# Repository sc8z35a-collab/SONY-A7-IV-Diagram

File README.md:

# @FLOW_BOOK 2: DOMAIN_SPEC (SONY-A7-IV-Diagram | FLOW-SPEC/v1.1)
> AUDIENCE=AI_AGENTS_ONLY | COMPANION=AGENTS.md (Book 1: ENV_OS) | QUERY: `npm run flow -- doc section 2 <@TAG>`

## @PROJECT_MAP
- App: Sony A7 IV Full-Frame Mirrorless Camera + Special Showcases (`welcome` WLK-435 CNC optical signboard, `original` Exhibit #01 RIIMOS E1 9,700 JPY quadruped, `mirai_2028` 2028 Frontier concepts, `sensor_fab` 6-vol semiconductor fab) 3D CAD WebGL2 Technical Anatomy + Play Ground 1.1 Studio (`PLYA V2.1`).
<!-- @FLOW_AUTO:PROJECT_METRICS -->
- Stack: TypeScript 5.8.2 + Three.js 0.174.0 + Vite 6.2.0 (`dist/` -> `docs/`) + Capacitor 7.6.10 (`android/`).
- Scale: 23 modes (21 individual + 2 composite), 2,937 unique individual parts (3,473 total entries incl. composites), PLYA V2.1 (24 browser solvers / 256 assertions).
<!-- /@FLOW_AUTO:PROJECT_METRICS -->
- Schematics & Rigs: 720x470 HD SVG schematics (`src/ui/schematicsRegistry.ts`), 60fps physics rigs.
- Protected Content Assets (NOT operational manuals): `reports/fh_mirai_2028/*.md` (compiled by `scripts/build_mirai_content.mjs`) and `blueprints/riimos_e1/` (RIIMOS E1 MJCF/Colab/blueprint assets).

## @RENDER_V2_V3_AND_PLYA_V21
- Universal V2 (`src/core/v2_unit_compiler.ts`): All units except bespoke `src/units/mi_shoe.ts` compile via `CompiledV2Unit` -> `ResourceCache` 38 PBR buckets (`src/core/resource_cache.ts`, 0 raw materials), `InstancedMesh`/`BatchedMesh`, flat TypedArray AABB-BVH (`bvhNodes`, stride 8) O(log N) 0-GC raycast, GPU shader explode, `disposeObject3D` VRAM leak=0, plus live cryptographic **`V1.1証明`** verifier (`src/core/v11_seal_verifier.ts`, `src/units/v1_1_certificates.gen.ts`) & clickable HUD warranty modal (`src/ui/ZeroTextControls.ts`).
- 4 Quality Tiers: `standard_lite` (Dual-Atlas Single-Bucket Fusion, ~2-8 draw calls, 16-bit Uint16 IBOs <=65k verts, Fresnel rim, spatial-hash weld); `standard`/`high`/`ultra` (progressive radial segments, 9k/18k/32k batched CAD edges, PMREM IBL, ULTRA zero-jaggy AA).
- Play Ground 1.1 + **`PLYA V2.1 (THE LAST EXAM V1.1 Inherited)`**: `src/playground/CadPlaygroundStudio.ts`, `PlyaVerificationPipeline.ts`, `exam_core/BrowserPhysicsSolvers.ts`, `exam_core/V11BrowserSolversExt.ts`. **12 Pillars / 24 Browser Solvers / 256 Atomic Assertions (`PG-T001..PG-T256`)**, Real-World Boot Readiness % & Six-Sigma Manufacturing Yield % meters, `.tlx11.json` export (`TLX11-PLAYGROUND-BLUEPRINT-V1.1`, bit-exact 0.0001mm canonical 3D SHA-256 parity with `ir_compiler.mjs`), `.v1_1.cert.json` import + **instant automatic V1.1証明 revocation on ANY 3D edit**.
- V3 10 Pillars: Play Ground 1.1 Hyper-Engine (40.05x avg speedup, 0.0 idle draws/s); STD LITE v2 (14.45x arith / 3.23x geo, 0.00% black-crush); ULTRA zero-jaggy AA; Adaptive `FAST<->LITE<->ULTRA` & `PG_FAST<->PG_LITE<->PG_SHARP`; `KINE` 3-layer 0-GC occlusion culling; 16x macro zoom; Load-guarded F1.2 bokeh (`auto`); Vivid electric-blue selection (`CAD_SELECT_SENTINEL`); Mobile 390x844@2 landscape UI & 90-deg lightbox; Locked camera angle in detail view.

## @UNIT_REGISTRY (23 MODES: mode | kind | parts | slug | codes | exam | entry | data)
- `welcome` | indiv | 435 | `welcome-` | W01..W435 | YES | `src/units/welcome.ts` | `src/data/welcome.json`
- `original` | indiv | 128 | `orig-` | OR01..OR128 | YES | `src/units/original.ts` | `src/data/original.json`
- `mishoe` | indiv | 99 | `mi-` | MI01..MI99 | YES | `src/units/mi_shoe.ts`* | `src/data/mi_shoe.json`
- `battery` | indiv | 130 | `bat-` | P01..P130 | YES | `src/units/battery.ts` | `src/data/battery.json`
- `cfexpress` | indiv | 170 | `cfe-` | C01..C170 | YES | `src/units/cfexpress.ts` | `src/data/cfexpress.json`
- `mic` | indiv | 150 | `mc-` | MC01..MC150 | YES | `src/units/mic.ts` | `src/data/mic.json`
- `drybox` | indiv | 186 | `db-` | DB01..DB186 | YES | `src/units/drybox.ts` | `src/data/drybox.json`
- `mount` | indiv | 100 | `mount-` | M22..M100 | YES | `src/units/mount.ts` | `src/data/mount.json`
- `shutter` | indiv | 180 | `shutter-` | SH34..SH180 | YES | `src/units/shutter.ts` | `src/data/shutter.json`
- `body` | indiv | 116 | `body-` | B01..B116 | YES | `src/units/body.ts` | `src/data/body.json`
- `evf` | indiv | 105 | `evf-` | E26..E105 | YES | `src/units/evf.ts` | `src/data/evf.json`
- `lcd` | indiv | 150 | `lcd-` | D01..D150 | YES | `src/units/lcd.ts` | `src/data/lcd.json`
- `lens` | indiv | 128 | `lens-` | L01..L128 | YES | `src/units/lens.ts` | `src/data/lens.json`
- `mainboard` | indiv | 60 | `mb-` | M17..M60 | YES | `src/units/mainboard.ts` | `src/data/mainboard.json`
- `bionz` | indiv | 70 | `xr-` | XR01..XR70 | YES | `src/units/bionz.ts` | `src/data/bionz.json`
- `bionz_v2` | indiv | 105 | `xv2-` | X2-01..X2-105 | YES | `src/units/bionz_v2.ts` | `src/data/bionz_v2.json`
- `sensor` | indiv | 120 | `sensor-` | S35..S120 | YES | `src/units/sensor.ts` | `src/data/sensor.json`
- `micro` | indiv | 75 | `micro-` | M12..M75 | YES | `src/units/micro.ts` | `src/data/micro.json`
- `micro_v2` | indiv | 55 | `pv2-` | P2-01..P2-55 | YES | `src/units/micro_v2.ts` | `src/data/micro_v2.json`
- `sensor_fab` | indiv | 235 | `fab5-` | F0-01..F5-38 | EXCL | `src/units/sensor_fab.ts` | `src/data/sensor_fab.json`
- `mirai_2028` | indiv | 140 | `mirai-` | FH01-01..FH48-18 | EXCL | `src/units/mirai_2028.ts` | `src/data/mirai_2028.json`
- `integrated` | comp | 305 | - | - | YES | `src/units/integrated.ts` | `src/data/integrated.json`
- `camera_body` | comp | 231 | - | - | YES | `src/units/camera_body.ts` | `src/data/camera_body.json`
- Note `*`: `mi_shoe.ts` implements `OptimizedUnit` directly, calls `applyUnitPoseTable()`, and attaches `v11Certification` for 23/23 parity.
- Sub-views: `lensSection=1..3`, `fabVolume=0..5`, `miraiSubView=1..5` (`beginner|expert`), `original` RIIMOS E1 (128p, 9,700 JPY BOM, 0.135J 8-barrel quadruped, L4 MJCF).

## @UNIT_DEPENDENCY_DAG (21 EXAM TARGETS + 2 EXCLUDED)
- **Stage 1 — 19 Independent EXAM Units (parallel-safe)**: `welcome, original, mishoe, battery, cfexpress, mic, drybox, mount, shutter, body, evf, lcd, lens, mainboard, bionz, bionz_v2, sensor, micro, micro_v2`.
- **Stage 2 — 2 Composite EXAM Units (MUST run AFTER Stage 1)**: `camera_body` (231p, depends on 7 Stage-1 builders: `mount, body, evf, shutter, sensor[macroParts], mainboard, lcd`) and `integrated` (305p, depends on all 8 Stage-1 builders: `lens, mount, body, evf, shutter, sensor[macroParts], mainboard, lcd`) via shared `src/units/camera_macro_shared.ts`.
- **EXAM Excluded (`EXCLUDED_EXAM_UNITS`)**: `mirai_2028` (140p), `sensor_fab` (235p).
<!-- @FLOW_AUTO:UNIT_HEALTH_SUMMARY -->
- Live Health Baseline (SSOT `catalog/UNIT_HEALTH.tsv` + `verification/certificates/` + `src/units/*.pose.tsv`): **Certified=`0/21`** | **Full-Clean (0 clash & 0 EX02 >0.08mm gap)=`0/21`** (`none`) | **0-Clash/Explode=`2/21`** (`welcome, original`) | **Pose=`0` rows (0u)**.
- Spatial Totals (`sp ultra` + `explode-8` + `EX02 0.08mm BFS`): `clash=13816`, `ex02_gap08=381`, `sp_float4=0`, `smt=81`, `explode=5224` | Top clash: `lcd:3102, shutter:2194, cfexpress:1563, integrated:1029, battery:813` | Instant read (<150ms): `npm run flow -- status --raw`.
<!-- /@FLOW_AUTO:UNIT_HEALTH_SUMMARY -->

## @CODE_3LAYER
- Layer G (`src/units/<U>.pose.tsv`, `src/core/flow_pose_loader.ts`): `id\tdx,dy,dz\trx,ry,rz\tsx,sy,sz\texp_dx,dy,dz\tmat_override\tconstraints`. Identical across `CompiledV2Unit`, `mi_shoe.ts`, and `scene_extractor.mjs` (0.000mm parity).
- Layer M (pure geometry `src/assemblies/<U>/*.ts`, `src/core/cad_primitives.ts`, slim `src/assemblies/types.ts` + auto-gen `diagram_types.gen.ts`): top `@FLOW_MAP` header, 0 duplicate prose (`lazyExplanationStub(id)`).
- Layer L (`src/data/<U>.json`): compact 1-part-per-line JSON (196k -> ~3.6k lines, -98%).
- Indexes (`catalog/`): `INDEX.tsv`, `UNIT_HEALTH.tsv`, `names/<U>.txt`, `ALL_NAMES.txt`, `spatial/<U>.tsv`, `code/{MAP,SYMBOLS,GRAPH,MATERIALS,HELPERS,SCHEMATICS,CSS_INDEX,DEFECT_MAP}.tsv`.
- Coordinates: Right-handed Y-up, 1 unit = 1 mm; grounded feet near global `minY`; optical axis `+Z`.

## @EXAM_V11_DOMAIN (SSOT Auto-Synced from `scripts/exam/test_registry.mjs`)
<!-- @FLOW_AUTO:EXAM_METRICS -->
- Live Totals (SSOT `test_registry.mjs`): **12 Pillars / 48 Engines / 1080 Fixed Tests (`T001..T1080`) / 48 Real Solvers / 28 Cross-Locks (`X01..X28`)**.
- Per-Pillar Counts: `P01:112t(5e) P02:114t(5e) P03:44t(2e) P04:136t(6e) P05:49t(2e) P06:96t(4e) P07:90t(4e) P08:44t(2e) P09:40t(2e) P10:79t(4e) P11:138t(6e) P12:138t(6e)`.
- C++17 Native Harnesses (6): `bullet_ode_multibody`, `cgal_geom_kernel`, `dart_kinematics_dynamics`, `fcl_ccd_router`, `occt_step_analyzer`, `spectral_gts_nlopt`.
- Wire Protocol: `TLX1|u=...|v=1.1|mode=CAD_PROXY|REAL_ARTIFACT|...|rcpt=TLX11-RECEIPT:...|v11_cert=...`, `V11_SEAL|unit=...|status=...|attest=CI_ATTESTED|LOCAL_UNATTESTED`.
<!-- /@FLOW_AUTO:EXAM_METRICS -->
- Pillars Overview: P01 Geom/Contact (EX01-05), P02 FEA (EX06-10), P03 Multibody/Fatigue (EX25-26), P04 DFM/DFA/Fasteners (EX11-14, EX27-28), P05 Thermal/CFD (EX29, EX15), P06 Power/EDA/Wiring/FMEA (EX16-17, EX30-31), P07 EMC/Optics/Acoustics (EX18-21), P08 Formal/RTL (EX32-33), P09 Chem/Rel (EX34-35), P10 Vision/BOM/GPU/Domain (EX22-24, EX36), P11 Real-World Boot/Control/SI/ESD (EX37-42), P12 Mfg/Tribology/Kinematics/Cert (EX43-48).
- Execution Modes: `MODE=CAD_PROXY` (3D CAD model verification) vs `MODE=REAL_ARTIFACT` (`--project=<exam.project.json>` real STEP/KiCad/SPICE/RTL/BOM; missing artifacts fail honestly as `MISSING_REAL_ARTIFACT`, ZERO fabrication). Verification vs Validation boundary is explicitly displayed in certificates and UI modal.
- 28 Cross-Solver Conservation Locks `X01..X28`: X01..X16 (core conservation) + X17(ngspice=gnucap inrush<=3%), X18(Octave=Maxima Routh=0), X19(Verilator=Icarus=GHDL RTL=0), X20(Z3=CVC5=Boolector=MiniSat UNSAT=0), X21(GetDP=FreeFEM EM/SI<=5%), X22(ngspice=GetDP ESD<=5%), X23(DART=Bullet=ODE torque<=3%), X24(CVXOPT=HiGHS LP<=1%), X25(CCX=OpenFOAM transient T<=8%), X26(FFTW3=SciPy PSD<=2%), X27(CGAL=OCCT=ADMesh=GTS vol<=2%), X28(Pint=SymPy=Maxima=mpmath SI<=0.01%).

### @EXAM_CERT_AND_PASS_CONTRACT (NO-SOURCE-LOOKUP THRESHOLDS & RUNTIME)
- **`V1.1証明`**: `fullRun=1`, 48e/1080t/28x/48sv READY, **`FAIL=0 & WARN=0 & ERR=0 & SKIP=0`** (1 WARN blocks). Auto-revokes on 0.0001mm 3D/pose/mat edit or kernel drift -> `verification/certificates/<U>.v1_1.cert.json` + `v1_1_certificates.gen.ts`.
- **Thresholds**:
  - P01(EX01-05): 4-tier clash=0, containment=0, SMT<=0.25mm, EX02 seat<=0.08mm, foot cop<=0.10mm FAIL(T055)/<=0.05mm WARN(T127), protrude=0, SMT poke=0(chassis XZ±1.5mm), CoG in hull, tip>=15°(lat>=20°) FAIL & >=26.6°(tan>=0.5) WARN(T139), cantilever<=1.0, cog_h<=0.55 WARN(T145), 6-view islands=1, CGAL manifold/0-self-int/0-inv, tris>=4/part.
  - P02-05(EX06-15,25-29): 16-step explode=0; fasteners & seals >=2 contacts(<=0.08mm), 0 air fasteners, thread>=1.5d; DFM(EX13) min wall: cnc>=0.50mm, cast>=0.80mm, glass>=0.30mm, elastomer/pcb/sheet>=0.04mm, razor>=0.15mm, cncAccess>=0.65, slender<=120/zeroDraft<=50 WARN; CalculiX f1>=80Hz/f2>=120Hz WARN, hasCompliant(elastomer clears T100/111/112), bow<=0.05mm/drop<=100G/slip<=2.5mm/fret<=0.25mm WARN, Miner<0.25; CFD T-limit & TIM<=0.08mm.
  - P06-12(EX16-24,30-48): ERC&DRC=0; cones occ=0%; Helmholtz 150..6000Hz, eig1>500Hz, dp<=15Pa, <=20dBA, panel_rattle=0, |fHelm-f1|/fHelm>=0.12 WARN(T423); galvanic >0.50V=0, Mg-Cu=0, >0.25V<=20 WARN(T460), dew>=5°C, MTBF>=50kh; Chrome+OpenCV 1 island, JSON==3D, tsc=0, docs/index.html(T510 WARN), 4-tier mono tris, GPU<=64MB; ADMesh 0 degen, Cp/Cpk>=1.33, Hertz SF>=1.5/p0<=1200MPa/wear<=2.5um, igraph 1-comp(<=0.12mm), screw_pierce=0.
- **VM (2vCPU/8GB)**: `exam setup` cold ~3-5m / warm <5s / `--verify-only` <0.3s; `exam --unit=<U>` ~15-45s/unit (`scheduler.mjs` resume).

### @EXAM_IR_FLAGS_AND_MATERIAL_DB (EXACT COMPILER RULES — ZERO SOURCE LOOKUP)
- **`PART_FLAGS` Regexes** (lowercase `id+title+subtitle+category+role`):
  - GROUNDED(1<<0): minY<=sceneMinY+1.2mm, or `rubber-feet|foot|feet|base-pad|tripod-socket|bottom-weight|leveling` within minY+2.5mm.
  - CHASSIS(1<<1): `chassis|frame|housing|shell|bezel|cover|plate|base|plinth|bulkhead|barrel|mount|cradle|endcap|beam|backplate|dock|socket|bracket|carrier`.
  - FASTENER(1<<2): `screw|bolt|washer|nut|pin|dowel|rivet|clip|spring|clamp|fastener|collar|dovetail|retainer|shim|snap`.
  - PCB(1<<3): `pcb|board|mainboard|mcpcb|substrate|fpc|flex` (not `shield|can`).
  - HEAT_SOURCE(1<<4): `led-array|led|bionz|isp|npu|mcu|cortex|pmic|charger|amp|dac|driver|sensor-die|cmos|laser|heater|motor|servo`. powerW: isp/bionz/npu/soc=3.2, cmos=1.4, servo/motor=1.2, pmic/charger=0.9, oled/lcd=0.7, led=0.5, else=0.15 (welcome: led-array=1.55, pmic=0.85, mcu=0.65, driver=0.25, amp=0.20, else=0.12).
  - ELASTOMER(1<<5): `gasket|seal|oring|o-ring|rubber|boot|damper|foam|elastomer|tim|thermal-pad|foot|feet|eyecup|grip` (hasCompliant=true).
  - OPTICAL(1<<6): `lens|glass|quartz|sapphire|prism|lgp|diffuser|window|filter|olpf|mirror|bef|polarizer|optical|ed-|xa-|led-array`.
  - CONDUCTOR(1<<7): `busbar|harness|wire|cable|coax|pogo|contact|terminal|trace|copper|fpc|antenna|wifi|ble|nfc|usbc|usb-c|hdmi|connector|canfd|fuse|inductor|supercap|battery|lifepo4|cell`.
  - MOVABLE(1<<8): `shutter-blade|dial|ring|hinge|tilt|lever|button|switch|toggle|leg|joint|servo|rotor|gear|focus-group|ibis-stage|actuator`.
  - SMT(1<<9): `ic|mcu|pmic|canfd|dac|amp|sensor|tof|lux|tcxo|rtc|eeprom|flash|esd|tvs|shunt|fuse|mlcc|inductor|resistor|capacitor|diode|mosfet|regulator|ferrite|transceiver` (if not PCB/CHASSIS).
- **Material Lookup**: `mesh.matKey` -> `CATALOG_KEY_TO_PRESET`; untagged -> `partId+title` regex -> default `a6061_t6`.
- **Presets (rho, E_GPa, sy_MPa, eGalv, mfgClass)**:
  - Metals: a6061_t6(2.7,69,276,-0.76V,cnc), ti6al4v(4.43,114,880,-0.05V,cnc), az91d_mg(1.81,45,160,-1.60V,cast), sus304(7.93,193,215,-0.08V,cnc), steel_hrc60(7.85,210,1200,-0.45V,cnc), invar36(8.1,141,275,-0.20V,cnc), copper_c1100(8.96,117,220,+0.18V,cnc), brass_c3604(8.5,97,310,-0.15V,cnc), becu_c17200(8.25,131,1000,-0.10V,sheet), w80cu20(15.6,260,550,+0.10V,cnc), gold_au(19.3,79,200,+0.35V,sheet), nickel_silver_emi(8.7,130,320,-0.12V,sheet), ndfeb_n52(7.5,160,80,-0.50V,sinter), sac305_solder(7.4,51,35,-0.45V,solder).
  - Insulators (eGalv=null, 0 galvanic risk): pa66_gf30(1.36,8.5,140,polymer), epdm_gasket(1.25,0.015,12,elastomer), tim_silicone_pad(2.6,0.008,3,elastomer), ptfe_washer(2.2,0.5,23,polymer), fr4_hdi_pcb(1.9,22,260,pcb), polyimide_fpc(1.42,3.2,110,pcb), ic_emc_epoxy(1.85,20,90,polymer), alumina_ceramic(3.9,370,300,ceramic), bk7/silica/sapphire(optical_glass), pmma_lgp(polymer), silicon_die(semi). Composites: cfrp_blade(+0.15V), pyro_graphite(+0.20V), lifepo4_cell(-0.80V).
  - Galvanic (EX34): dV=|eGalvA-eGalvB|; >0.50V FAIL (az91d_mg vs Cu/SUS/Ti/Au -> isolate with pa66_gf30/epdm_gasket/ptfe_washer or match alloy).

### @EXAM_DEBUG_PLAYBOOK (ZERO-SOURCE-READ FIX RECIPES)
1. **Entry**: Run `flow exec exam query <runId> --status=FAIL` (`--status=WARN`) + `flow inspect <id> --defect --unit=<U>` for exact metric/parts/src=file:line. NEVER open `scripts/exam/**`!
2. **GOLDEN RULE — Fix EX02 (<=0.08mm) Cascade FIRST**: `sp` only flags >4.0mm; EX02 requires 1 connected component at <=0.08mm (incl. internal multi-mesh submeshes). Any >0.08mm gap cascades FAIL across **200+ downstream tests** (EX03/06/07/09/12/14-19/21/25/32/35/36/44/48). Fix EX01 clashes + `ex02_gap08` (`flow status` + `flow heal --apply`) FIRST!
3. **EX03-05/46**: Align GROUNDED feet minY<=0.05mm, no dips below sceneMinY-0.05mm, non-optical SMT inside chassis XZ±1.5mm, cog_h<=0.55, widen stance for tipMin>=26.6°; no zero-thickness/neg-scale/open/degenerate meshes.
4. **EX06-10 CalculiX**: Models largest XZ-footprint CHASSIS (L x W, H>=3mm, its E/nu/sy/rho). Thicken/stiffen primary chassis if f1<80Hz/f2<120Hz; keep >=1 ELASTOMER part for hasCompliant=true.
5. **EX11-14**: Distinct explode dirs; fasteners & seals need >=2 contacts <=0.08mm; avoid cnc_metal/cast_metal on <0.50/0.80mm CHASSIS trim.
6. **EX15/29/21 CFD/Acoustics**: heat_flux=totalPowerW/envelopeArea -> avoid HEAT_SOURCE keywords on passive parts; TIM gap<=0.08mm; keep fHelm >=12% off f1.
7. **EX22-24/36 GPU<=64MB**: Keep ultra tris <~1.3M (avoid multi-hole beveled ExtrudeGeometry frames; use thin perimeter walls); run `npm run build` for `docs/index.html`.
8. **EX47 Hertz Trap**: `spectral_gts_nlopt` uses `minYieldMpa = min(sy>20MPa)` across ALL CHASSIS|FASTENER parts (`hertzSf=1.6*minYieldMpa/hertzMaxMpa>=1.5`). NEVER put low-yield ptfe/pa66/sac305/ndfeb on a CHASSIS or FASTENER part!
9. **EX48 Screw Pierce & igraph**: Fails if ANY FASTENER AABB overlaps ANY PCB AABB >0.1mm in X & Z while Y overlaps `[pcb.minY-0.05, pcb.maxY+0.05]`. Mount PCB screws on perimeter bosses outside PCB AABB; ensure igraph <=0.12mm graph has 1 component.

## @PERF_AND_HISTORY
- V3 Baselines: Play Ground 1.1 `40.05x` avg speedup / `0.0 draws/s` idle; STD LITE v2 `14.45x` arith / `3.23x` geo, `welcome/lite=2dc/38.2k tris`, `integrated/lite=8dc/135.5k tris`, `maxLeakedCacheRefs=0`.
- History: P12-39 core 23u -> PR#53-62 V3, dx/sp/pp1.1/sokutei, RIIMOS E1, EXAM V1 -> PR#63 FLOW V1 OS -> PR#64 EXAM V1.1 + `V1.1証明` + PLYA V2.1 + auto/macro -> PR#65-66 Security Fortress (Permit, UserNS/NetNS+Docker, Keyless OIDC/Sigstore, 48-attack oracle, SSOT docs, 4-pillar speedup) -> **PR#67 Instant Comprehension Cold-Start OS & EXAM Parity Fixes** (`I00 NO_INFRA_DIVE` plan+debug, `@CONTRACTS_QUICKREF`, 8k-tok `README.md`, `catalog/UNIT_HEALTH.tsv` incl. `ex02_gap08`, `<150ms`/`<=450tok` zero-spill `flow status`, `wake --brief`, `@FLOW_AUTO:UNIT_HEALTH_SUMMARY`, `ir_compiler.mjs`/`scene_extractor.mjs` `matKey` & `buildSourceLineMap` fixes, `exam_setup.sh --verify-only`).

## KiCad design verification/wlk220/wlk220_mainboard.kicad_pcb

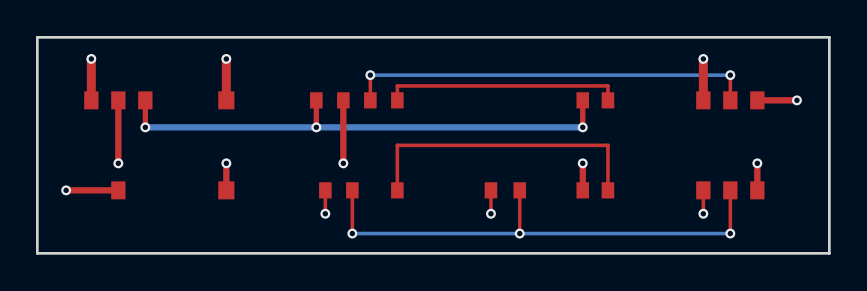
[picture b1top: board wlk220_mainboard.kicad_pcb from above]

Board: 4 copper layers, 44.0 x 12.0 mm, 6 parts (0 on the bottom side), 9 nets.

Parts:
C1: 720uF_POLY
J_BUS: GLYPH_BUS_HDR
R1: 120R_CAN
U2: PMIC_3RAIL
U4: STM32H743
U6: VL53L5CX_HDR

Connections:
+3V3_LOG: U2.3, U4.1, U6.1
+5V_AUD: J_BUS.3, U2.4
+12V_BUS: C1.1, J_BUS.1, U2.1
CANH: J_BUS.4, R1.1, U4.6
CANL: J_BUS.5, R1.2, U4.7
GND: C1.2, J_BUS.6, U2.2, U4.2, U6.4
I2C_SCL: U4.5, U6.3
I2C_SDA: U4.4, U6.2
PWM_SYNC: J_BUS.2, U4.3
